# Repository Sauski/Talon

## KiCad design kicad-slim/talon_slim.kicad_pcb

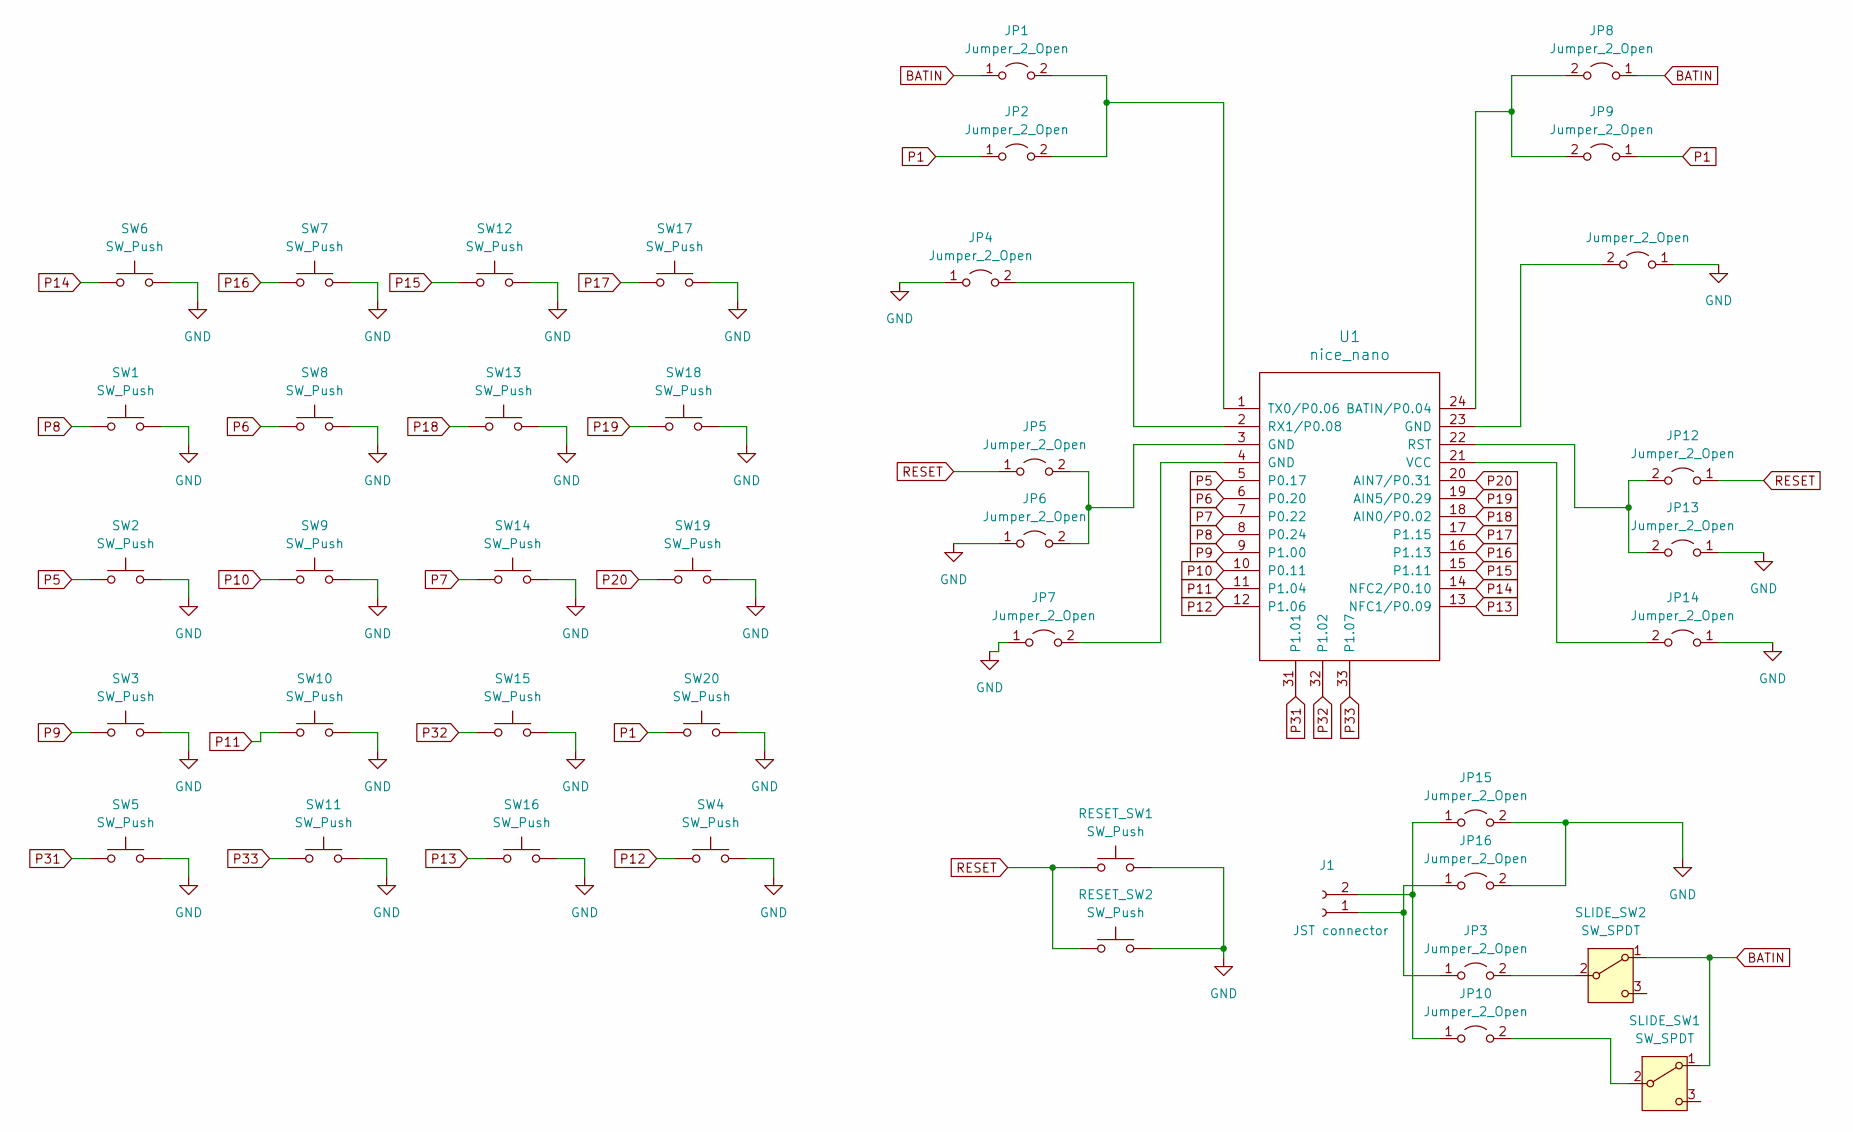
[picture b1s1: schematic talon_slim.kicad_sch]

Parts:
J1: JST connector; JST_PH_S2B-PH-K_1x02_P2.00mm_Horizontal
JP1, JP2, JP8, JP9: Jumper_2_Open; Jumper_Open_0.8mm
JP3, JP4, JP5, JP6, JP7, JP10, JP11, JP12, JP13, JP14, JP15, JP16: Jumper_2_Open; Jumper_Open_0.5mm
RESET_SW1, RESET_SW2: SW_Push; Panasonic_EVQPUL_EVQPUC
SLIDE_SW1, SLIDE_SW2: SW_SPDT; SW_SSSS811101
SW1, SW2, SW3, SW4, SW5, SW6, SW7, SW9, SW10, SW11, SW12, SW13, SW14, SW15, SW16, SW17, SW19, SW20: SW_Push; SW_PG1350_reversible
SW8, SW18: SW_Push; SW_PG1350_reversible_1.5U
U1: nice_nano

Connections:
BATIN: JP1.1 (A), JP8.1 (A), SLIDE_SW1.1 (A), SLIDE_SW2.1 (A)
GND: JP4.1 (A), JP6.1 (A), JP7.1 (A), JP11.1 (A), JP13.1 (A), JP14.1 (A), JP15.2 (B), JP16.2 (B), RESET_SW1.2, RESET_SW2.2, SW1.2, SW2.2, SW3.2, SW4.2, SW5.2, SW6.2, SW7.2, SW8.2, SW9.2, SW10.2, SW11.2, SW12.2, SW13.2, SW14.2, SW15.2, SW16.2, SW17.2, SW18.2, SW19.2, SW20.2
unnamed: J1.1, JP3.1 (A), JP16.1 (A)
unnamed: J1.2, JP10.1 (A), JP15.1 (A)
unnamed: JP1.2 (B), JP2.2 (B), U1.1 (TX0/P0.06)
unnamed: JP3.2 (B), SLIDE_SW2.2 (B)
unnamed: JP4.2 (B), U1.2 (RX1/P0.08)
unnamed: JP5.2 (B), JP6.2 (B), U1.3 (GND)
unnamed: JP7.2 (B), U1.4 (GND)
unnamed: JP8.2 (B), JP9.2 (B), U1.24 (BATIN/P0.04)
unnamed: JP10.2 (B), SLIDE_SW1.2 (B)
unnamed: JP11.2 (B), U1.23 (GND)
unnamed: JP12.2 (B), JP13.2 (B), U1.22 (RST)
unnamed: JP14.2 (B), U1.21 (VCC)
P1: JP2.1 (A), JP9.1 (A), SW20.1
P5: SW2.1, U1.5 (P0.17)
P6: SW8.1, U1.6 (P0.20)
P7: SW14.1, U1.7 (P0.22)
P8: SW1.1, U1.8 (P0.24)
P9: SW3.1, U1.9 (P1.00)
P10: SW9.1, U1.10 (P0.11)
P11: SW10.1, U1.11 (P1.04)
P12: SW4.1, U1.12 (P1.06)
P13: SW16.1, U1.13 (NFC1/P0.09)
P14: SW6.1, U1.14 (NFC2/P0.10)
P15: SW12.1, U1.15 (P1.11)
P16: SW7.1, U1.16 (P1.13)
P17: SW17.1, U1.17 (P1.15)
P18: SW13.1, U1.18 (AIN0/P0.02)
P19: SW18.1, U1.19 (AIN5/P0.29)
P20: SW19.1, U1.20 (AIN7/P0.31)
P31: SW5.1, U1.31 (P1.01)
P32: SW15.1, U1.32 (P1.02)
P33: SW11.1, U1.33 (P1.07)
RESET: JP5.1 (A), JP12.1 (A), RESET_SW1.1, RESET_SW2.1

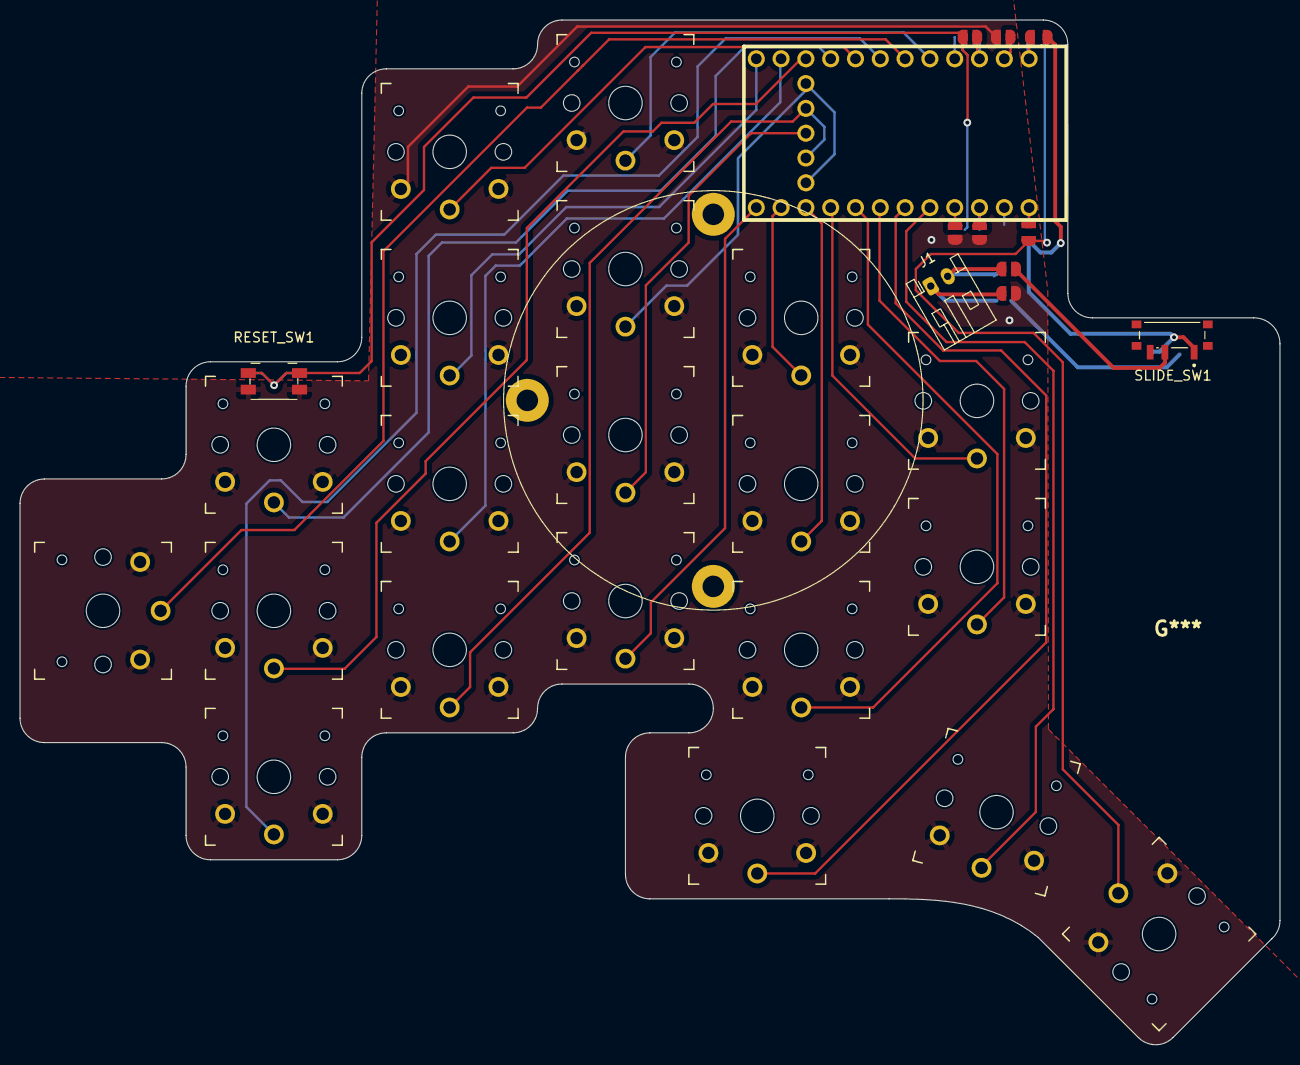
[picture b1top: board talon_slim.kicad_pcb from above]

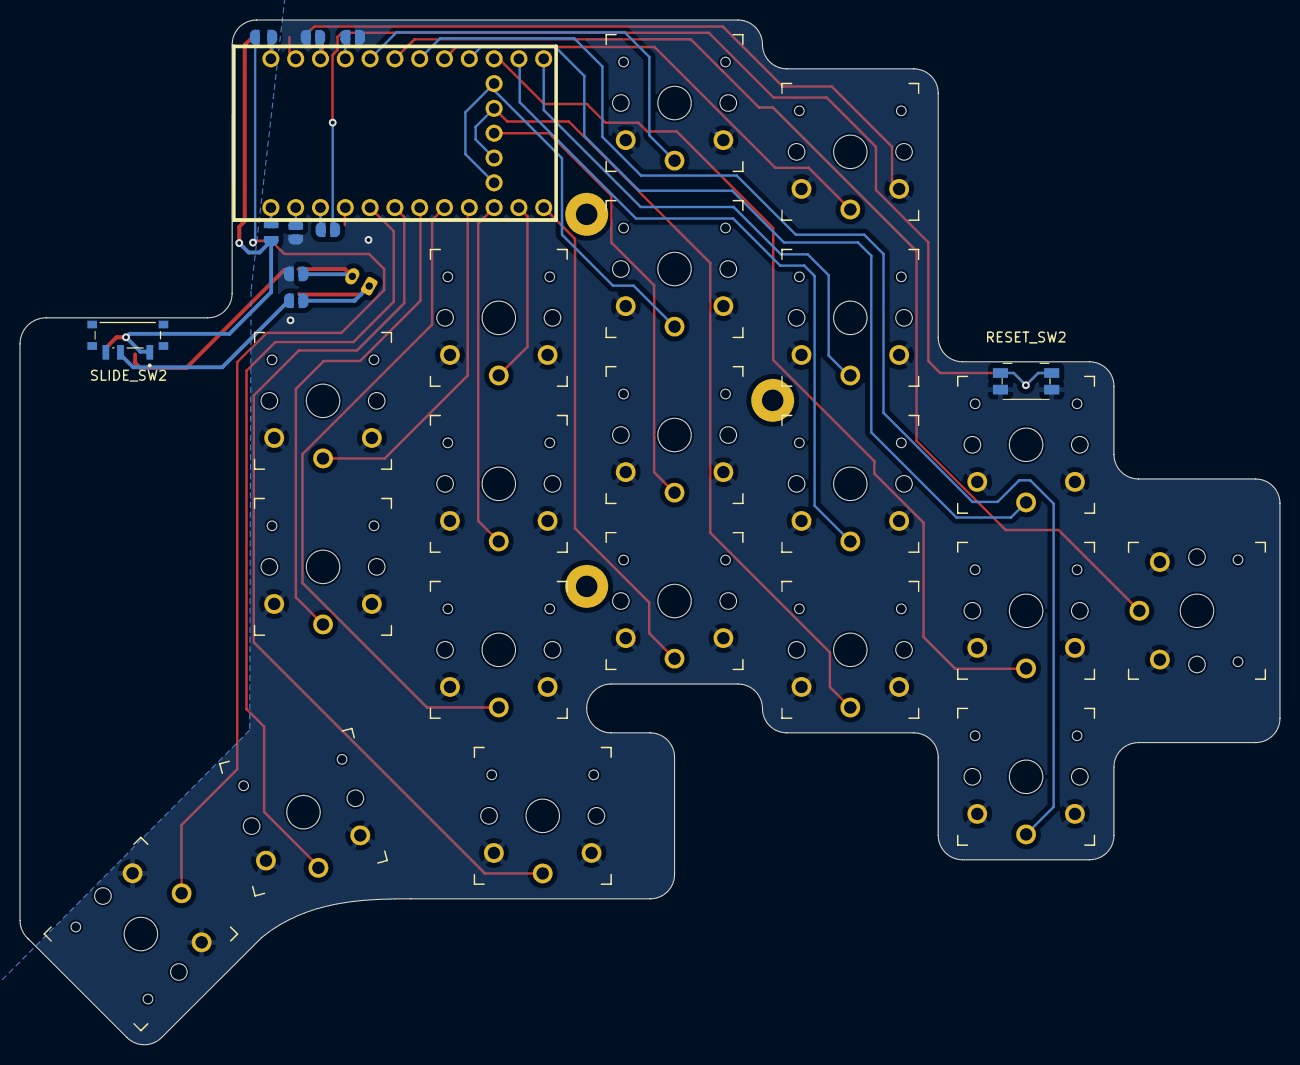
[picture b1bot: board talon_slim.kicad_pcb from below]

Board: 2 copper layers, 129.0 x 104.9 mm, 42 parts (10 on the bottom side), 35 nets.

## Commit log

2024-04-27 Initial sketch
2024-04-28 getting pretty tasty!
2024-04-28 fully constrained key plate
2024-04-28 add fillets to keyplate
2024-04-28 added fillet to pcb
2024-04-28 working on routing
    Battery connection gnd is disconnected from fill.
2024-04-28 PCB seems legit
2024-05-01 v1 sent for production
2024-05-12 Added json and started keymap
2024-05-18 Initally seems legit! Well fucking done......
2024-05-18 Keymap feeling pretty good
    Turns out curling the pinky is better
    Turns out curling the fingers is better.
    Fuck.
2024-12-25 We international now, baby!
2024-12-25 Add the Alternative International keyboard dee el els
2025-10-08 thinking about slim
2026-01-19 Slim looking not tooooo bad
2026-01-20 sent slim for procuction
